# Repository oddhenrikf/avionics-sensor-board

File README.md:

# Avionics sensor board

I'm interested in rocket avionics and wanted to design a board of my own to learn more about the hardware side. This is a four-layer sensor board built around an STM32 microcontroller, with motion and environmental sensors, USB-C and a 3.3 V power supply.
Please keep in mind that it is still revision 1... 

I worked on the component selection, schematic and PCB layout in KiCad. The aim is to get experience with the whole process, from reading datasheets and routing a board to assembling it and getting sensor readings back.

### 3D View

*KiCad 3D render. Some components may not have a 3D model.*

## Hardware

| Part | Purpose |
| --- | --- |
| STM32G474 | Microcontroller |
| BMI088 | Accelerometer and gyroscope |
| BME680 | Environmental sensor |
| TPS62162 | 3.3 V buck regulator |
| USB-C | Power and USB connection |
| Debug header | Programming and debugging |

## Where it is now

The schematic and PCB layout have been designed and sent for PCB manufacture. Assembly, firmware bring-up and testing are still ahead. This is a learning prototype, and I haven't validated it for use in flight.

My next steps are to assemble the board, check the power supply, connect a debugger and bring up the sensors one at a time. I'll document what works and what needs changing.

## Files

- [Schematic preview](images/v1.svg)
- [KiCad project](hardware/v1.kicad_pro)
- [Schematic source](hardware/v1.kicad_sch)
- [PCB layout](hardware/v1.kicad_pcb)
- [Project footprint library](hardware/v1_custom.pretty/)

To open it locally, download or clone the repository and open `hardware/v1.kicad_pro` in KiCad 10. Keep `fp-lib-table` and `v1_custom.pretty` beside the project files. The original project filename is still `v1`.

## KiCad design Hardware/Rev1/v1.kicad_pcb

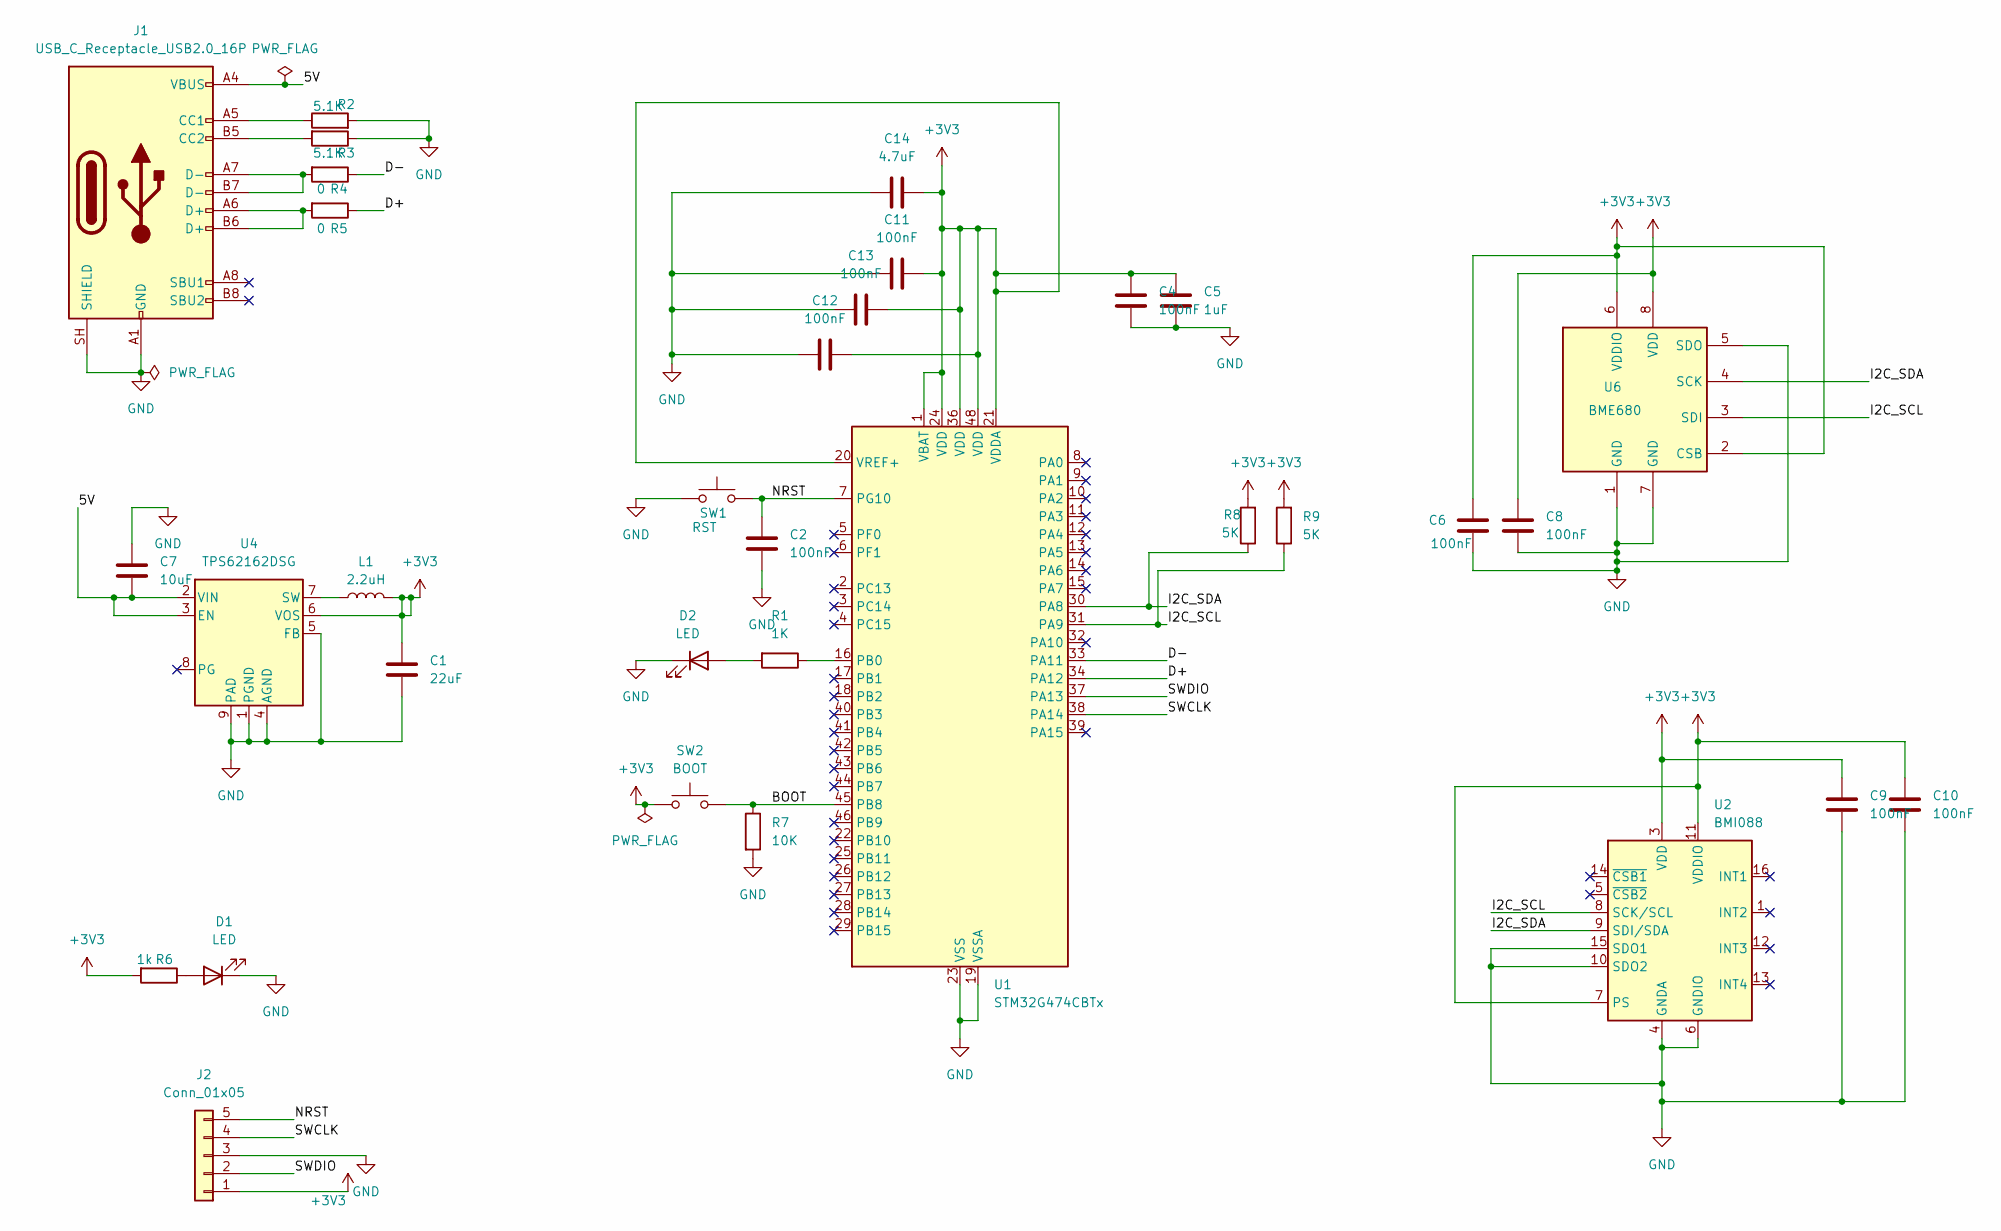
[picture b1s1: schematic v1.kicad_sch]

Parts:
C1: 22uF; C_1206_3216Metric_Pad1.33x1.80mm_HandSolder
C2, C4, C6, C8, C9, C10, C11, C12, C13: 100nF; C_0805_2012Metric_Pad1.18x1.45mm_HandSolder
C5: 1uF; C_0805_2012Metric_Pad1.18x1.45mm_HandSolder
C7: 10uF; C_1206_3216Metric_Pad1.33x1.80mm_HandSolder
C14: 4.7uF; C_0805_2012Metric_Pad1.18x1.45mm_HandSolder
D1, D2: LED; LED_0805_2012Metric_Pad1.15x1.40mm_HandSolder
J1: USB_C_Receptacle_USB2.0_16P; USB4105_GND_Rounded35
J2: Conn_01x05; PinHeader_1x05_P2.54mm_Vertical
L1: 2.2uH; L_Coilcraft_XxL4020
R1: 1K; R_0805_2012Metric_Pad1.20x1.40mm_HandSolder
R2, R3: 5.1K; R_0805_2012Metric_Pad1.20x1.40mm_HandSolder
R4, R5: 0; R_0805_2012Metric_Pad1.20x1.40mm_HandSolder
R6: 1k; R_0805_2012Metric_Pad1.20x1.40mm_HandSolder
R7: 10K; R_0805_2012Metric_Pad1.20x1.40mm_HandSolder
R8, R9: 5K; R_0805_2012Metric_Pad1.20x1.40mm_HandSolder
SW1: RST; SW_PUSH_6mm
SW2: BOOT; SW_PUSH_6mm
U1: STM32G474CBTx; LQFP-48_7x7mm_P0.5mm
U2: BMI088; Bosch_LGA-16_4.5x3mm_P0.5mm_LayoutBorder7x1y_ClockwisePinNu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
U4: TPS62162DSG; WSON-8-1EP_2x2mm_P0.5mm_EP0.9x1.6mm_ThermalVias
U6: BME680; Bosch_LGA-8_3x3mm_P0.8mm_ClockwisePinNumbering

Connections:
+3V3: C1.1, C4.1, C5.1, C6.1, C8.1, C9.1, C10.1, C11.2, C12.2, C13.2, C14.2, J2.1, L1.2, R6.2, R8.2, R9.2, SW2.1, U1.1 (VBAT), U1.20 (VREF+), U1.21 (VDDA), U1.24 (VDD), U1.36 (VDD), U1.48 (VDD), U2.3 (VDD), U2.7 (PS), U2.11 (VDDIO), U4.6 (VOS), U6.2 (CSB), U6.6 (VDDIO), U6.8 (VDD)
/5V: C7.2, J1.A4 (VBUS), J1.A9 (VBUS), J1.B4 (VBUS), J1.B9 (VBUS), U4.2 (VIN), U4.3 (EN)
/BOOT: R7.1, SW2.2, U1.45 (PB8)
/D+: R5.1, U1.34 (PA12)
/D-: R4.1, U1.33 (PA11)
/I2C_SCL: R9.1, U1.31 (PA9), U2.8 (SCK/SCL), U6.3 (SDI)
/I2C_SDA: R8.1, U1.30 (PA8), U2.9 (SDI/SDA), U6.4 (SCK)
/NRST: C2.1, J2.5, SW1.2, U1.7 (PG10)
/SWCLK: J2.4, U1.38 (PA14)
/SWDIO: J2.2, U1.37 (PA13)
GND: C1.2, C2.2, C4.2, C5.2, C6.2, C7.1, C8.2, C9.2, C10.2, C11.1, C12.1, C13.1, C14.1, D1.1 (K), D2.1 (K), J1.A1 (GND), J1.A12 (GND), J1.B1 (GND), J1.B12 (GND), J1.SH (SHIELD), J2.3, R2.2, R3.1, R7.2, SW1.1, U1.19 (VSSA), U1.23 (VSS), U1.35 (VSS), U1.47 (VSS), U2.2 (GNDA), U2.4 (GNDA), U2.6 (GNDIO), U2.10 (SDO2), U2.15 (SDO1), U4.1 (PGND), U4.4 (AGND), U4.5 (FB), U4.9 (PAD), U6.1 (GND), U6.5 (SDO), U6.7 (GND)
unnamed: D1.2 (A), R6.1
unnamed: D2.2 (A), R1.2
unnamed: J1.A5 (CC1), R2.1
unnamed: J1.B5 (CC2), R3.2
unnamed: J1.A6 (D+), J1.B6 (D+), R5.2
unnamed: J1.A7 (D-), J1.B7 (D-), R4.2
unnamed: R1.1, U1.16 (PB0)
unnamed: L1.1, U4.7 (SW)

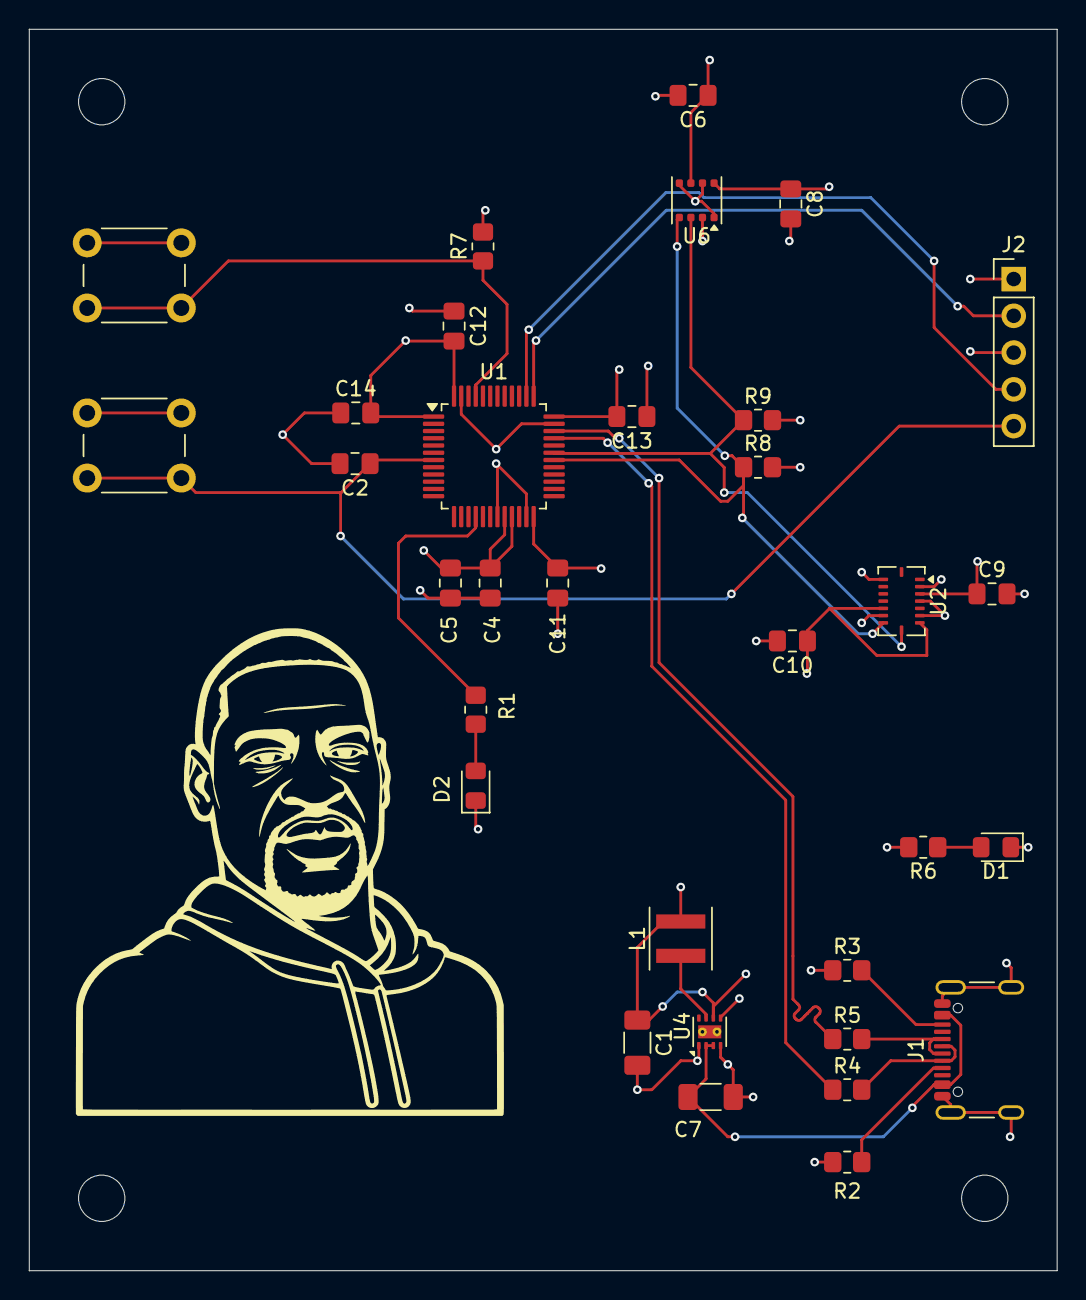
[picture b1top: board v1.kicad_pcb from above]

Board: 4 copper layers, 71.0 x 85.8 mm, 37 parts (0 on the bottom side), 19 nets.

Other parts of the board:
H1, H2, H3, H4: MountingHole_3.2mm_M3
